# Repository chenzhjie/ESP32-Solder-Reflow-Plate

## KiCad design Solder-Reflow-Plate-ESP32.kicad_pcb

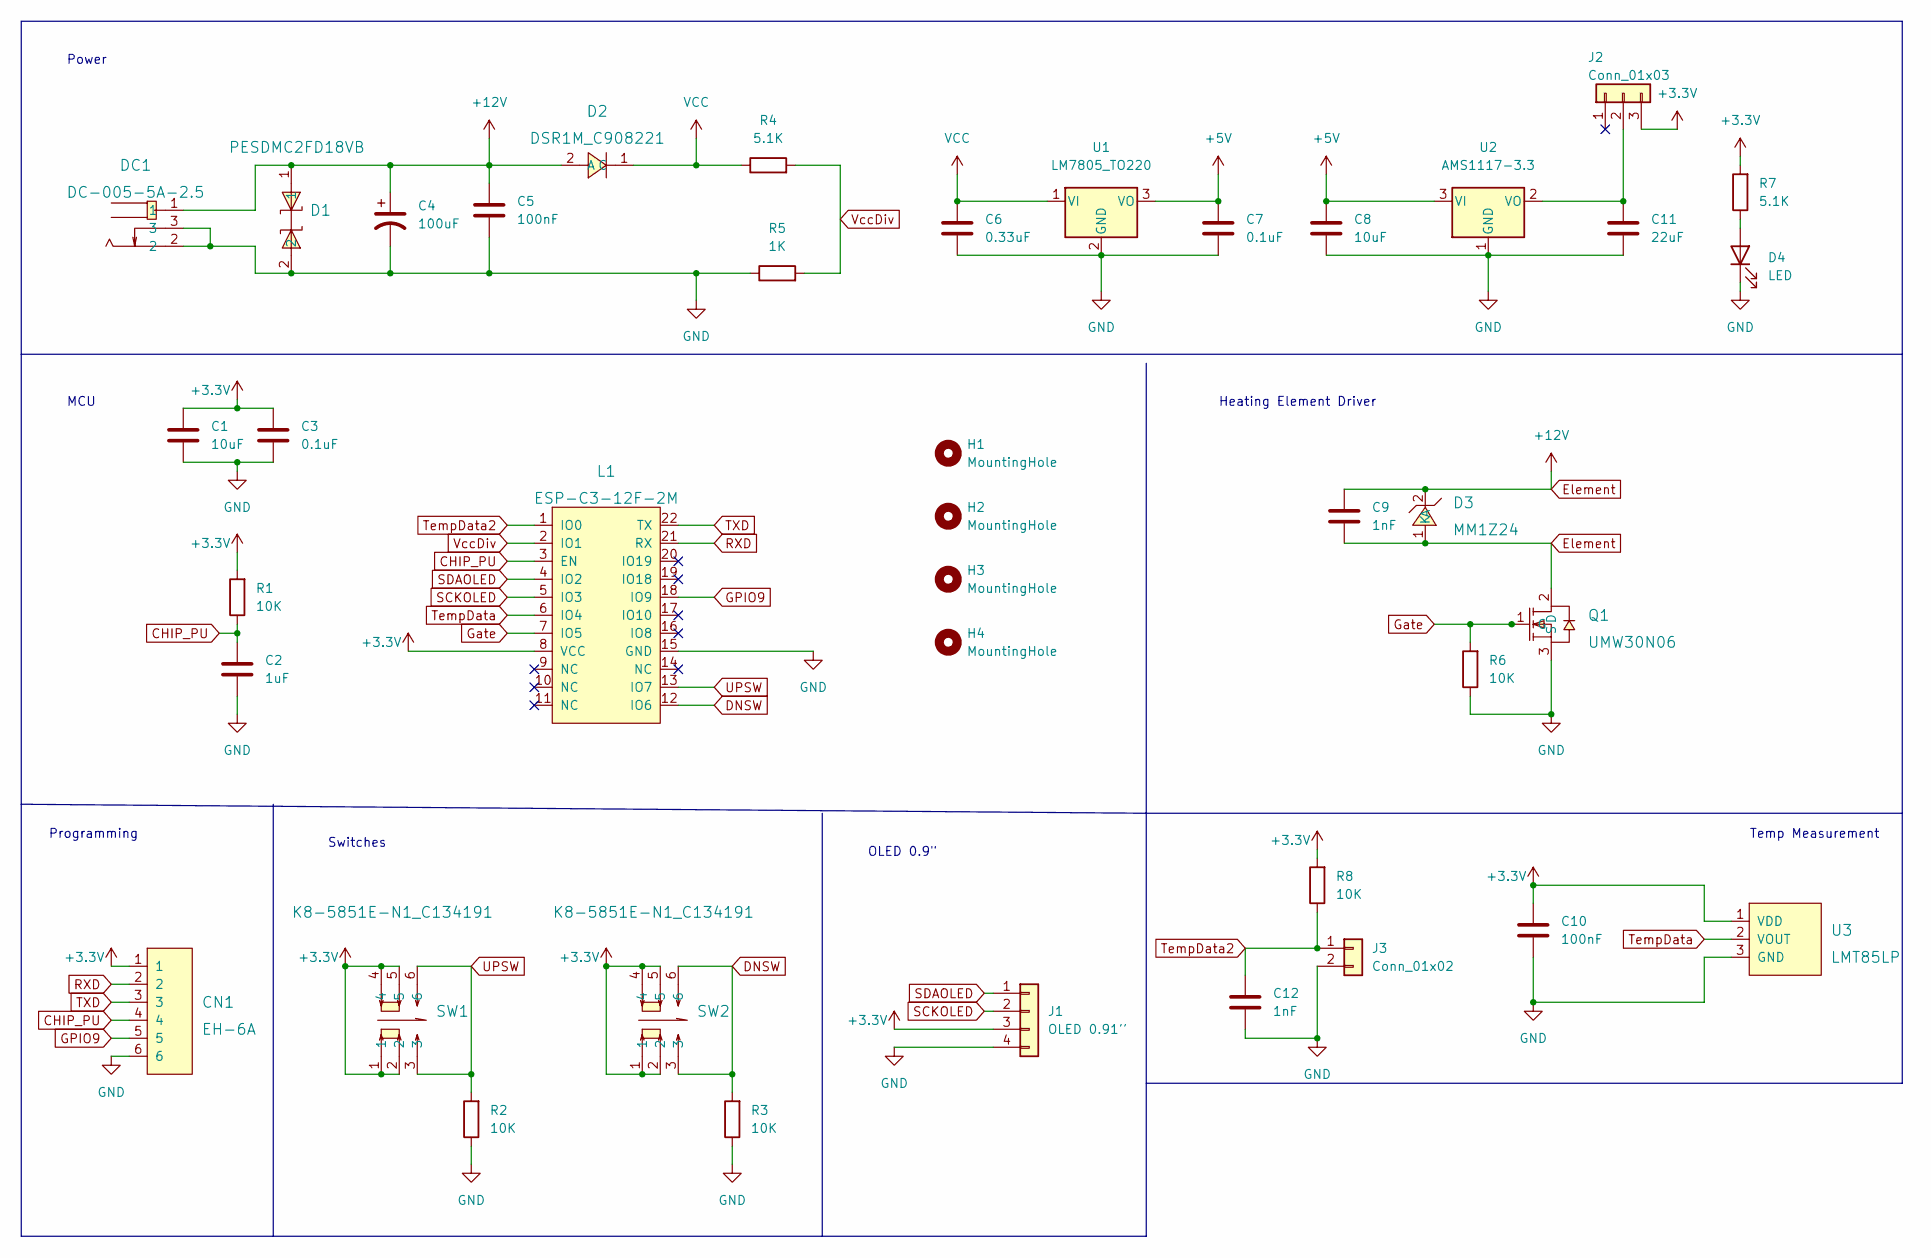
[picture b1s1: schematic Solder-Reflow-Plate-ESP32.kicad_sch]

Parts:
C1, C8: 10uF; C_0805_2012Metric_Pad1.18x1.45mm_HandSolder
C2: 1uF; C_0603_1608Metric_Pad1.08x0.95mm_HandSolder
C3: 0.1uF; C_0603_1608Metric_Pad1.08x0.95mm_HandSolder
C4: 100uF; CAP-SMD_BD6.3-L6.6-W6.6-LS7.6-FD
C5, C10: 100nF; C_0603_1608Metric_Pad1.08x0.95mm_HandSolder
C6: 0.33uF; C_0805_2012Metric_Pad1.18x1.45mm_HandSolder
C7: 0.1uF; C_0805_2012Metric_Pad1.18x1.45mm_HandSolder
C9, C12: 1nF; C_0805_2012Metric_Pad1.18x1.45mm_HandSolder
C11: 22uF; C_0805_2012Metric_Pad1.18x1.45mm_HandSolder
CN1: EH-6A; CONN-TH_EH-6A; LCSC Part C64410
D1: PESDMC2FD18VB; X1-DFN1006-2_L1.0-W0.6-RD; LCSC Part C110703
D2: DSR1M_C908221; SOD-123_L2.8-W1.8-LS3.7-RD; LCSC Part C908221
D3: MM1Z24; SOD-123_L2.8-W1.8-LS3.7-FD; LCSC Part C82522
D4: LED; LED_0603_1608Metric_Pad1.05x0.95mm_HandSolder
DC1: DC-005-5A-2.5; DC-IN-TH_DC-005-5A-2.5; LCSC Part C381115
H1, H2, H3, H4: MountingHole; MountingHole_3.2mm_M3
J1: OLED 0.91''; PinSocket_1x04_P2.54mm_Vertical
J2: Conn_01x03; PinHeader_1x03_P2.54mm_Vertical
J3: Conn_01x02; PinHeader_1x02_P2.54mm_Vertical
L1: ESP-C3-12F-2M; WIRELM-SMD_ESP-C3-12F-2M; LCSC Part C2847302
Q1: UMW30N06; TO-252-2_L6.6-W6.1-P4.57-LS9.9-BR-CW; LCSC Part C369599
R1, R2, R3, R6: 10K; R_0603_1608Metric_Pad0.98x0.95mm_HandSolder
R4: 5.1K; R_0805_2012Metric_Pad1.20x1.40mm_HandSolder
R5: 1K; R_0805_2012Metric_Pad1.20x1.40mm_HandSolder
R7: 5.1K; R_0603_1608Metric_Pad0.98x0.95mm_HandSolder
R8: 10K; R_0805_2012Metric_Pad1.20x1.40mm_HandSolder
SW1, SW2: K8-5851E-N1_C134191; SW-TH_6P-L5.8-W5.8-P2.00-LS4.5-BL; LCSC Part C134191
U1: LM7805_TO220; TO-220-3_Vertical
U2: AMS1117-3.3; SOT-223-3_TabPin2
U3: LMT85LP; TO-92-3_L4.9-W3.7-P1.27-L; LCSC Part C75856

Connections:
+3V3: C1.1, C3.1, C10.1, CN1.1, J1.3, J2.3, L1.8 (VCC), R1.2, R7.2, R8.2, SW1.1, SW1.2, SW1.4, SW1.5, SW2.1, SW2.2, SW2.4, SW2.5, U3.1 (VDD)
+5V: C7.1, C8.1, U1.3 (VO), U2.3 (VI)
CHIP_PU: C2.1, CN1.4, L1.3 (EN), R1.1
DNSW: L1.12 (IO6), R3.2, SW2.3, SW2.6
Element: C4.1, C5.1, C9.1, C9.2, D1.1, D2.2 (A), D3.1 (A), D3.2 (K), DC1.1, Q1.2 (D)
GND: C1.2, C2.2, C3.2, C4.2, C5.2, C6.2, C7.2, C8.2, C10.2, C11.2, C12.2, CN1.6, D1.2, D4.1 (K), DC1.2, DC1.3, J1.4, J3.2, L1.15 (GND), Q1.3 (S), R2.1, R3.1, R5.1, R6.1, U1.2 (GND), U2.1 (GND), U3.3 (GND)
GPIO9: CN1.5, L1.18 (IO9)
Gate: L1.7 (IO5), Q1.1 (G), R6.2
unnamed: C11.1, J2.2, U2.2 (VO)
unnamed: D4.2 (A), R7.1
RXD: CN1.2, L1.21 (RX)
SCKOLED: J1.2, L1.5 (IO3)
SDAOLED: J1.1, L1.4 (IO2)
TXD: CN1.3, L1.22 (TX)
TempData: L1.6 (IO4), U3.2 (VOUT)
TempData2: C12.1, J3.1, L1.1 (IO0), R8.1
UPSW: L1.13 (IO7), R2.2, SW1.3, SW1.6
VCC: C6.1, D2.1 (C), R4.1, U1.1 (VI)
VccDiv: L1.2 (IO1), R4.2, R5.2

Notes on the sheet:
Power
Switches
Temp Measurement
Heating Element Driver
OLED 0.9"
Programming
MCU

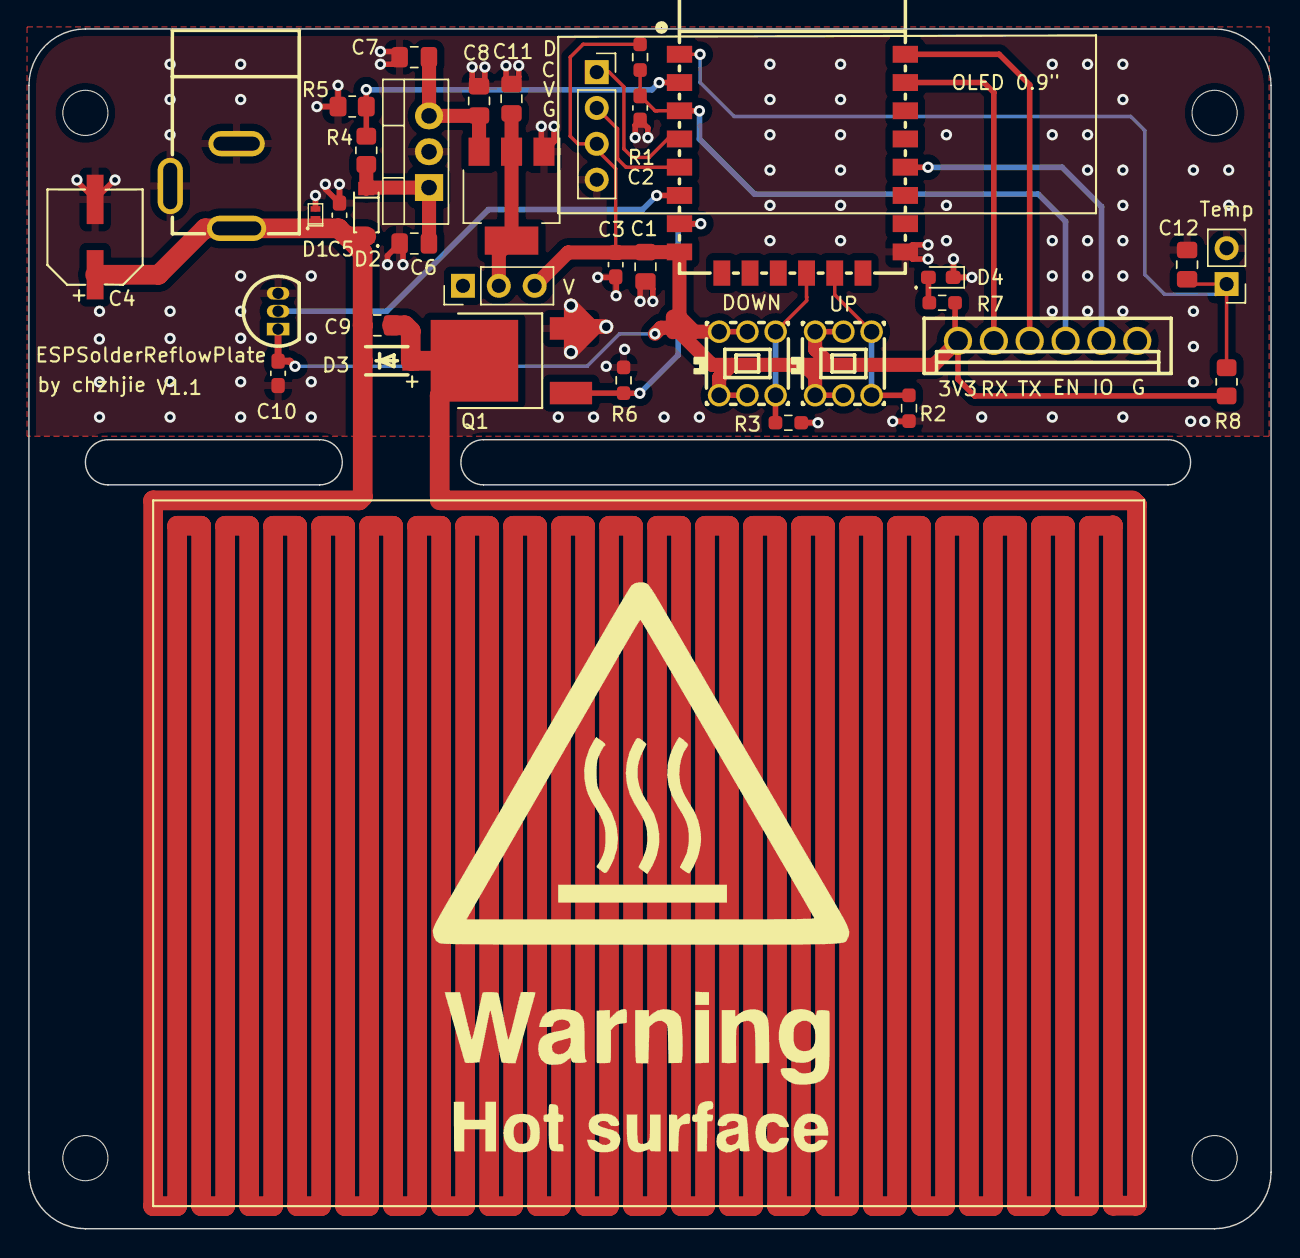
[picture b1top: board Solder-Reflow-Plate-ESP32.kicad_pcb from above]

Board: 2 copper layers, 88.0 x 85.0 mm, 40 parts (0 on the bottom side), 19 nets.

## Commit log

2022-06-03 init
